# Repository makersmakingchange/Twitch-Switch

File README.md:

<!---  Open Source Assistive Technology: GitHub Readme Template Version 1.1 (2024-Mar-15)  --->

<!--- INSTRUCTIONS This is a markdown template for creating the README.md file in a GitHub repository. This file is rendered and displayed automatically when someone visits the repository.  --->  
 
 <!---  TITLE Should match the name of the GitHub repository. Choose something descriptive rather than whimsical.   --->
# Twitch Switch

<!---  SUMMARY A brief summary of the project. What it does, who it is for, how much it costs.  --->
The Twitch Switch is for users with limited movement capabilities. Up to three small wireless sensors can capture very small movements. The Twitch Switch can be used for activating up to three switch adapted devices or emulating a mouse or keyboard to operate a digital device such as a computer. 

The Twitch Switch works best for someone who is only able to perform small movements. There are three sensors that can be placed wherever the user has the most controlled, repeatable, intentional movement. Sensor placement can include on the user's finger, wrist, foot, or head. The sensors are powered by rechargeable batteries and connect wirelessly to a controller. The sensitivity of each sensor can be adjusted using knobs on the controller.

The first way to use the Twitch Switch allows the user to activate up to 3 switch adapted devices. Whenever the corresponding switch is moved (even slightly!), the switch adapted device will be activated. 
The second way to use the Twitch Switch is for controlling a digital device such as a computer, tablet, or smartphone. The Twitch Switch can connect via Bluetooth or USB, and has 3 modes: mouse mode, tablet mode, and keyboard mode (which is best for switch control).

The Twitch Switch is intended primarily for people who have some controlled, repeatable, intentional movement, but otherwise have limited mobility and/or dexterity. This device may be beneficial for users with cerebral palsy (CP), spinal cord injuries (SCI), amyotrophic lateral sclerosis (ALS), muscular dystrophy (MD), locked-in syndrome (LIS), traumatic brain injury (TBI), or other disabilities or conditions that significantly limit movement.

The total cost of materials to build this device is around \$360 (plus component shipping). The cost of materials per unit is around \$200 (plus component shipping) if you are able to build in bulk.

Note: for those located in Canada who are interested in this device, there are a limited number of Twitch Switches available free of cost. Please contact the Rehabilitation Engineering Department at the Stan Cassidy Centre for Rehabilitation at SCCRRehabEngineering@horizonnb.ca

## More info at
- [Makers Making Change Assistive Device Library Listing](https://www.makersmakingchange.com/s/product/twitch-switch/01tJR000003UiebYAC)

## How to Obtain the Device
### 1. Do-it-Yourself (DIY) or Do-it-Together (DIT)

This is an open-source assistive technology, so anyone is free to build it. All of the files and instructions required to build the device are contained within this repository. Refer to the Maker Guide below.

### 2. Request a build of this device

You may also submit a build request through the [Makers Making Change Assistive Device Listing](https://www.makersmakingchange.com/s/product/twitch-switch/01tJR000003UiebYAC) to have a volunteer maker build the device. As the requestor, you are responsible for reimbursing the maker for the cost of materials and any shipping.

### 3. Build this device for someone else

If you have the skills and equipment to build this device, and would like to donate your time to create the device for someone who needs it, visit the [MMC Maker Wanted](https://makersmakingchange.com/maker-wanted/) section.

## Build Instructions

### 1. Read through the Maker Guide

The [Maker Guide](/Documentation/Twitch_Switch_Maker_Guide.pdf) contains all the necessary information to build this device, including tool lists, assembly instructions, programming instructions and testing.

### 2. Order the Custom PCBs

This build requires two customs PCBS: one custom PCB for the controller and one custom PCB for each of the three sensors. The sensor PCB has a number of surface mount components and it is recommended to have the PCB fabricator assemble these components on the board.

### 3. Order the Off-The-Shelf Components

The [Bill of Materials](/Documentation/Twitch_Switch_BOM.csv) lists all of the parts and components required to build the device.

### 4. Print the 3D Printable components

All of the files and individual print files can be in the [/Build_Files/3D_Printing_Files](/Build_Files/3D_Printing_Files/) folder. Instructions and settings are provided in the 3D Printing Guide section of the [Maker Guide](/Documentation/Twitch_Switch_Maker_Guide.pdf).

### 5. Assemble the Twitch Switch

Reference the [Maker Guide](/Documentation/Twitch_Switch_Maker_Guide.pdf) for the tools and steps required to build each portion.

## How to improve this Device
As open source assistive technology, you are welcomed and encouraged to improve upon the design. 

## Files
### Documentation
| Document             | Version | Link |
|----------------------|---------|------|
| Maker Guide          | 1.0     | [Twitch Switch_Maker_Guide](/Documentation/Twitch_Switch_Maker_Guide.pdf)     |
| Bill of Materials    | 1.0     | [Twitch Switch_Bill_of_Materials](/Documentation/Twitch_Switch_BOM.csv)     |
| User Guide           | 1.0     | [Twitch Switch_User_Guide](/Documentation/Twitch_Switch_User_Guide.pdf)    |
| Changelog            | 1.0     | [Changelog](CHANGES.txt)     |

### Design Files
<!--- DESIGN FILES Include a copy of the original design files to facilitate easy editing and customization. Consider also including a generic format (e.g., STEP) --->
 - [CAD Files](/Design_Files/CAD_Design_Files)
 - [PCB Files](/Design_Files/PCB_Design_Files)

<!--- BUILD FILES Include a copy of the build files intended for manufacturing. This may include svg files for laser cutting, stl files for 3d printing, Gerber files for custom PCBs, and Arduino files for custom firmware --->
### Build Files
 - [3D Printing Files](/Build_Files/3D_Printing_Files)
 - [PCB Build Files](/Build_Files/PCB_Build_Files)
 - [Firmware Files](/Build_Files/Firmware_Files)

<!--- ATTRIBUTION Provide any necessary attribution for designs or components that are included in the device or as part of the project. --->
## Attribution

The Twitch Switch was designed by the Rehabilitation Engineering Department at Horizon Health's, Stan Cassidy Centre for Rehabilitation (SCCR).  Development was supported through the Government of Canada's Innovation Science and Economic Development [Accessible Technology Program](https://ised-isde.canada.ca/site/accessible-technology-program). The ATP program enabled SCCR to deploy numerous Twitch Switches to users at reduced cost.

The latest design (V3.0) incorporates feedback and suggestions from numerous users, clinicians, and volunteer makers.

The latest design incorporates several commercially available open source hardware components from [Adafruit](https://www.adafruit.com/). The Twitch Switch firmware utilizes the [Arduino](https://www.arduino.cc/) development platform, and a number of libraries developed and shared by the open source community.

<!---
This is the attribution for the template.
--->
The documentation template was created by Makers Making Change / Neil Squire Society and is used under a CC BY-SA 4.0 license. It is available at the following link: [https://github.com/makersmakingchange/OpenAT-Template](https://github.com/makersmakingchange/OpenAT-Template)

<!--- CONTRIBUTORS List the names of the people that contributed to the design. This could include the original source of the idea, designers, testers, documenters, etc. --->
### Contributors
- Rachelle Bernier, Horizon Health Network. 
- Marla Calder, Horizon Health Network 
- Natasha Hanson, Horizon Health Network 
- Dorian Hawkes, Horizon Health Network 
- Rick McCaskill, Horizon Health Network 
- Billie O'Connor, Horizon Health Network 
- Kristen Culberson, Horizon Health Network 
- Josie Versloot, Neil Squire Society / Makers Making Change
 
<!--- LICENSE Add the year(s) for the copyright and the Designer Name. You may use the standard set of open licenses or choose your own for the hardware, software, and accompanying materials. --->
## License
Copyright (c) 2020-2024 Stan Cassidy Center for Rehabilitation.

This repository describes Open Hardware:
 - Everything needed or used to design, make, test, or prepare the Twitch Switch is licensed under the [CERN 2.0 Weakly Reciprocal license (CERN-OHL-W v2) or later](https://cern.ch/cern-ohl ) .
 - All software is under the [GNU General Public License v3.0 (GPL-3.0)](https://www.gnu.org/licenses/gpl.html).
 - Accompanying material such as instruction manuals, videos, and other copyrightable works that are useful but not necessary to design, make, test, or prepare the Twitch Switch are published under a [Creative Commons Attribution-ShareAlike 4.0 license (CC BY-SA 4.0)](https://creativecommons.org/licenses/by-sa/4.0/) .

You may redistribute and modify this documentation and make products using it under the terms of the [CERN-OHL-W v2](https://cern.ch/cern-ohl).
This documentation is distributed WITHOUT ANY EXPRESS OR IMPLIED WARRANTY, INCLUDING OF MERCHANTABILITY, SATISFACTORY QUALITY AND FITNESS FOR A PARTICULAR PURPOSE.
Please see the CERN-OHL-W v2 for applicable conditions.

Source Location: https://github.com/makersmakingchange/Twitch-Switch

---

<!-- ABOUT MMC START -->
## About Makers Making Change

Makers Making Change is a program of [Neil Squire](https://www.neilsquire.ca/), a Canadian non-profit that uses technology, knowledge, and passion to empower people with disabilities.

Makers Making Change leverages the capacity of community based Makers, Disability Professionals and Volunteers to develop and deliver affordable Open Source Assistive Technologies.

 - Website: [www.MakersMakingChange.com](https://www.makersmakingchange.com/)
 - GitHub: [makersmakingchange](https://github.com/makersmakingchange)
 - Bluesky: [@makersmakingchange.bsky.social](https://bsky.app/profile/makersmakingchange.bsky.social)
 - Instagram: [@makersmakingchange](https://www.instagram.com/makersmakingchange)
 - Facebook: [makersmakechange](https://www.facebook.com/makersmakechange)
 - LinkedIn: [Neil Squire Society](https://www.linkedin.com/company/neil-squire-society/)
 - Thingiverse: [makersmakingchange](https://www.thingiverse.com/makersmakingchange/about)
 - Printables: [MakersMakingChange](https://www.printables.com/@MakersMakingChange)

### Contact Us
For technical questions, to get involved, or to share your experience we encourage you to [visit our website](https://www.makersmakingchange.com/) or [contact us](https://www.makersmakingchange.com/s/contact).
<!-- ABOUT MMC END -->

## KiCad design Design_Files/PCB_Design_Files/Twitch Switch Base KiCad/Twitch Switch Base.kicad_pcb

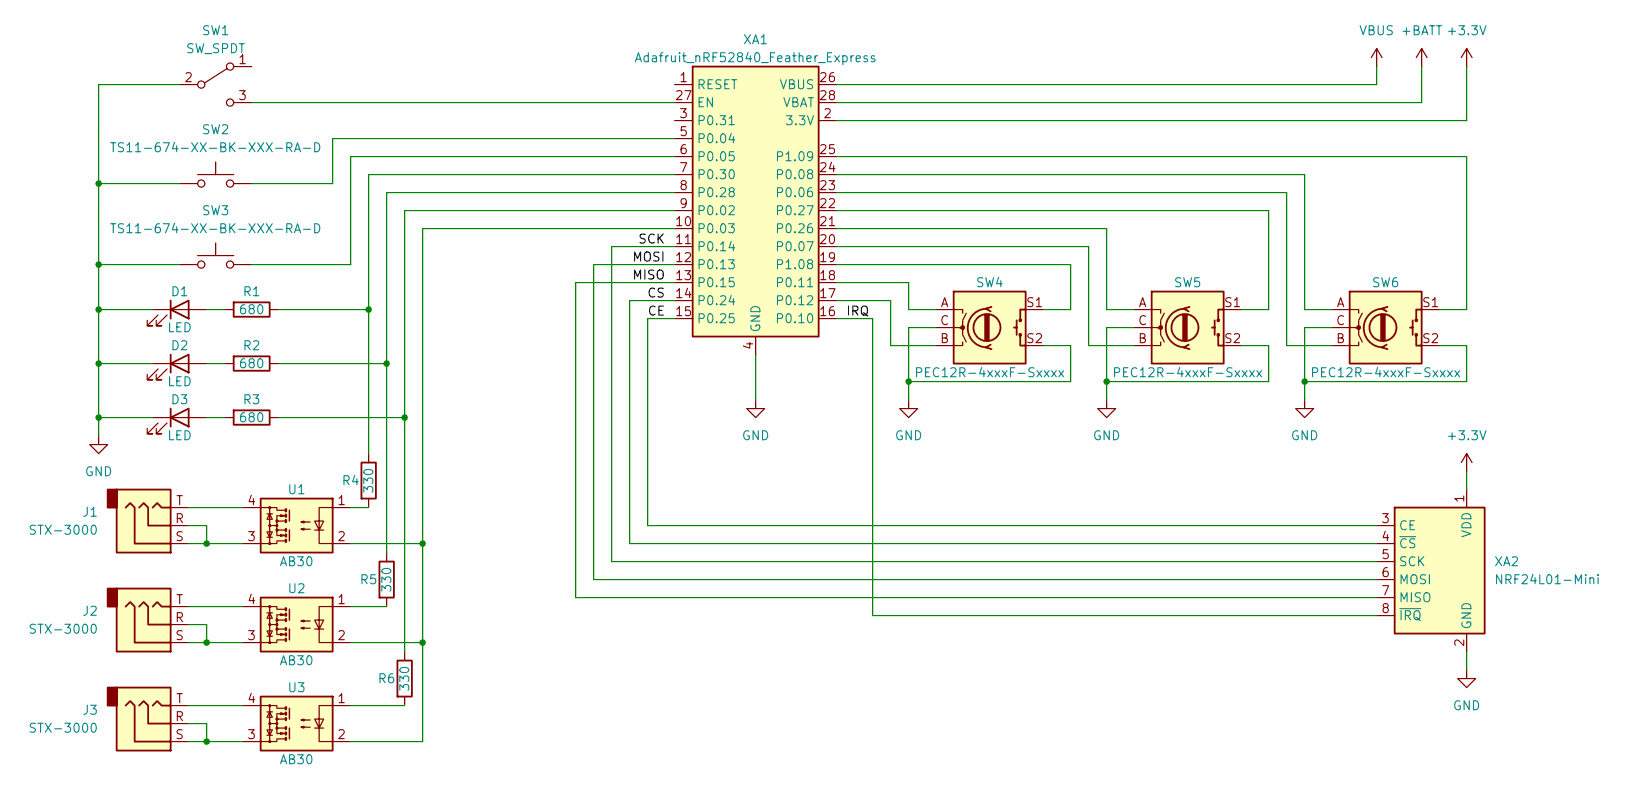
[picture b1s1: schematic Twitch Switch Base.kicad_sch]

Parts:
D1, D2, D3: LED; LED_D5.0mm
J1, J2, J3: STX-3000
R1, R2, R3: 680; R_Axial_DIN0207_L6.3mm_D2.5mm_P7.62mm_Horizontal
R4, R5, R6: 330; R_Axial_DIN0207_L6.3mm_D2.5mm_P7.62mm_Horizontal
SW1: SW_SPDT; CSS-1210TB
SW2, SW3: TS11-674-XX-BK-XXX-RA-D
SW4, SW5, SW6: PEC12R-4xxxF-Sxxxx
U1, U2, U3: AB30; DIP-4_W7.62mm
XA1: Adafruit_nRF52840_Feather_Express; Adafruit Feather nRF52840 Express
XA2: NRF24L01-Mini

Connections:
+3.3V: XA1.2 (3.3V), XA2.1 (VDD)
+BATT: XA1.28 (VBAT)
/CE: XA1.15 (P0.25), XA2.3 (CE)
/CS: XA1.14 (P0.24), XA2.4 (~CS)
/IRQ: XA1.16 (P0.10), XA2.8 (~IRQ)
/MISO: XA1.13 (P0.15), XA2.7 (MISO)
/MOSI: XA1.12 (P0.13), XA2.6 (MOSI)
/SCK: XA1.11 (P0.14), XA2.5 (SCK)
GND: D1.1 (K), D2.1 (K), D3.1 (K), SW1.2 (B), SW2.1, SW3.1, SW4.C, SW4.MP, SW4.S2, SW5.C, SW5.MP, SW5.S2, SW6.C, SW6.MP, SW6.S2, XA1.4 (GND), XA1.MNT1, XA1.MNT2, XA2.2 (GND), XA2.9 (GND)
unnamed: D1.2 (A), R1.2
unnamed: D2.2 (A), R2.2
unnamed: D3.2 (A), R3.2
unnamed: J1.R, J1.S, U1.3
unnamed: J1.T, U1.4
unnamed: J2.R, J2.S, U2.3
unnamed: J2.T, U2.4
unnamed: J3.R, J3.S, U3.3
unnamed: J3.T, U3.4
unnamed: R1.1, R4.1, XA1.7 (P0.30)
unnamed: R2.1, R5.1, XA1.8 (P0.28)
unnamed: R3.1, R6.1, XA1.9 (P0.02)
unnamed: R4.2, U1.1
unnamed: R5.2, U2.1
unnamed: R6.2, U3.1
unnamed: SW1.3 (C), XA1.27 (EN)
unnamed: SW2.2, XA1.5 (P0.04)
unnamed: SW3.2, XA1.6 (P0.05)
unnamed: SW4.A, XA1.18 (P0.11)
unnamed: SW4.B, XA1.17 (P0.12)
unnamed: SW4.S1, XA1.19 (P1.08)
unnamed: SW5.A, XA1.21 (P0.26)
unnamed: SW5.B, XA1.20 (P0.07)
unnamed: SW5.S1, XA1.22 (P0.27)
unnamed: SW6.A, XA1.24 (P0.08)
unnamed: SW6.B, XA1.23 (P0.06)
unnamed: SW6.S1, XA1.25 (P1.09)
unnamed: U1.2, U2.2, U3.2, XA1.10 (P0.03)
VBUS: XA1.26 (VBUS)

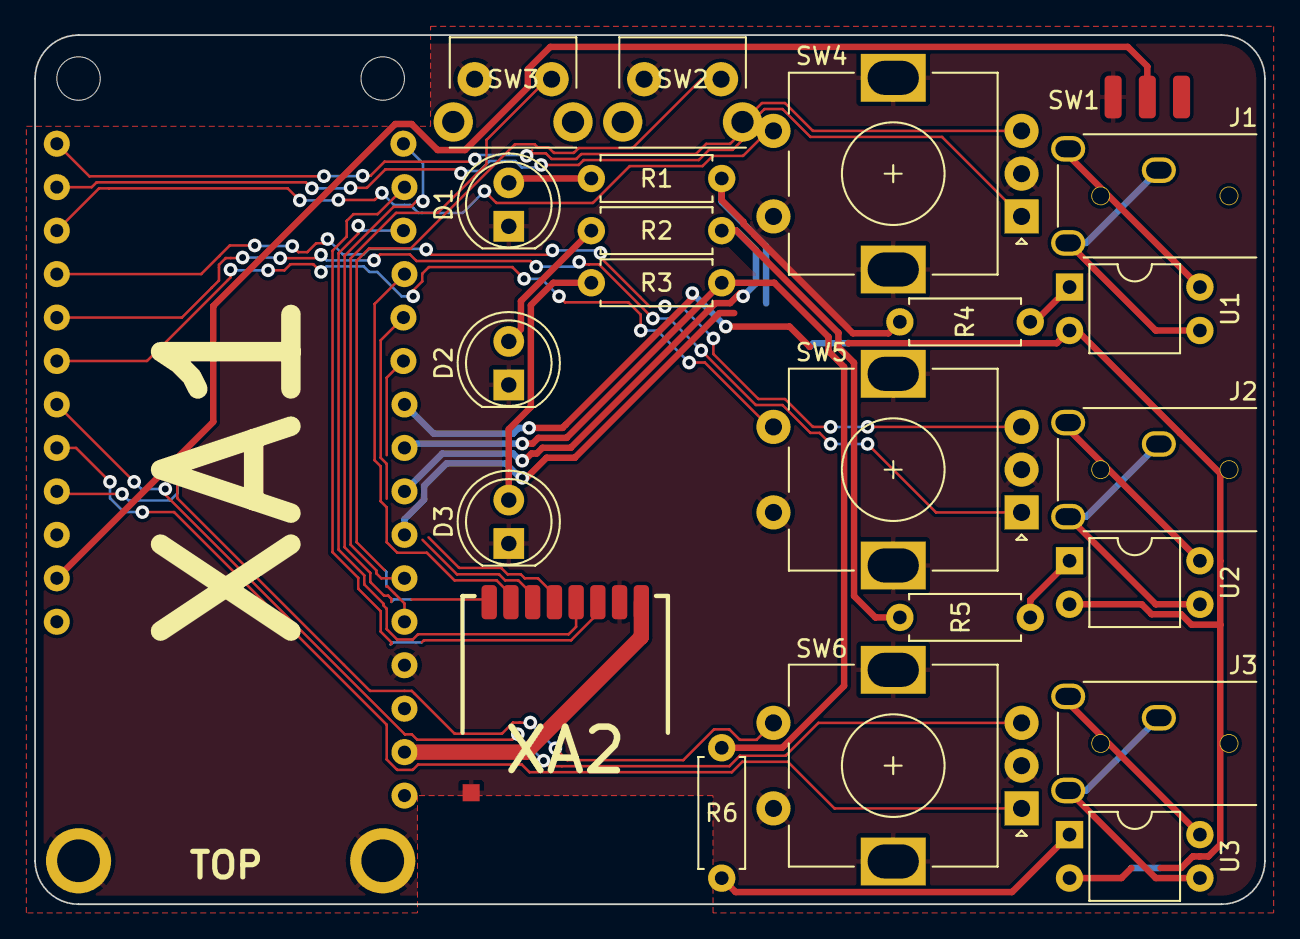
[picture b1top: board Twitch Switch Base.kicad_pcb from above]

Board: 2 copper layers, 71.9 x 50.8 mm, 23 parts (0 on the bottom side), 36 nets.

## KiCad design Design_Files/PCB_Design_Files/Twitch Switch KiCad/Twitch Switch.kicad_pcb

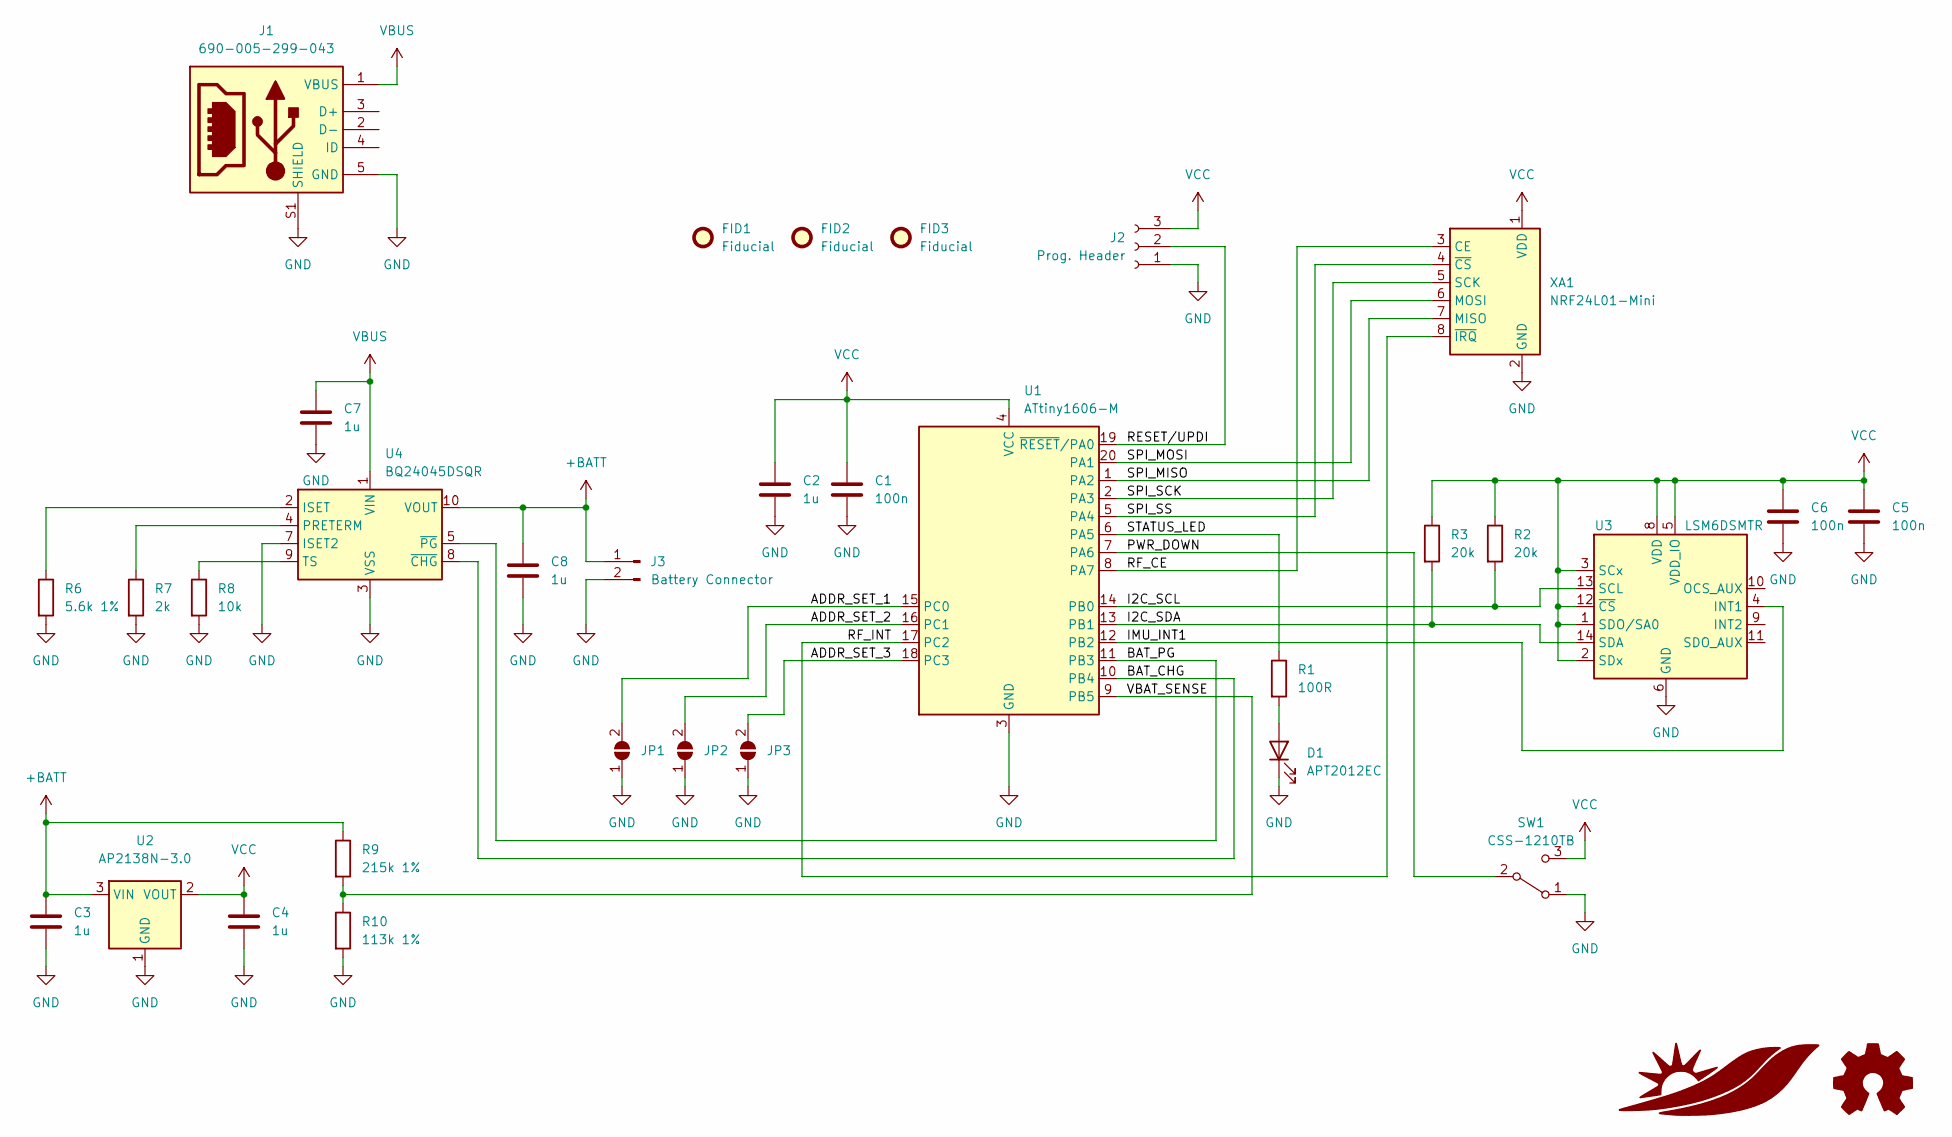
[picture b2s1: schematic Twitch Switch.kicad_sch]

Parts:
C1: 100n; C_0402_1005Metric; Part CL10B104KB8NNWC
C2, C3, C4, C7, C8: 1u; C_0402_1005Metric; Part CL10B105KP8NFNC
C5, C6: 100n; C_0402_1005Metric; Part CL10B105KP8NFNC
D1: APT2012EC; LED_0805_2012Metric; Part APT2012EC
FID1, FID2, FID3: Fiducial; Fiducial_0.5mm_Mask1mm
J1: 690-005-299-043
J2: Prog. Header; PinHeader_1x03_P2.54mm_Vertical
J3: Battery Connector; JST_PH_S2B-PH-K_1x02_P2.00mm_Horizontal; Part S2B-PH-K-S(LF)(SN)
JP1, JP2, JP3: SolderJumper_2_Open; SolderJumper-2_P1.3mm_Open_RoundedPad1.0x1.5mm
LOGO1: Logo_Open_Hardware_Small; OSHW-Logo_11.4x12mm_SilkScreen
LOGO2: Logo_Stan_Cassidy
R1: 100R; R_0402_1005Metric; Part RMCF0603JT100R
R2, R3: 20k; R_0402_1005Metric; Part RMCF0603JT20K0
R6: 5.6k 1%; R_0402_1005Metric; Part RMCF0603FT5K60
R7: 2k; R_0402_1005Metric; Part RMCF0603JT2K00
R8: 10k; R_0402_1005Metric; Part RMCF0603JT10K0
R9: 215k 1%; R_0402_1005Metric; Part RMCF0603FT215K
R10: 113k 1%; R_0402_1005Metric; Part RMCF0603FT113K
SW1: CSS-1210TB; Part CSS-1210TB
U1: ATtiny1606-M; VQFN-20-1EP_3x3mm_P0.4mm_EP1.7x1.7mm; Part ATtiny1606-MFR
U2: AP2138N-3.0; SOT-23; Part AP2138N-3.0TRG1
U3: LSM6DSMTR
U4: BQ24045DSQR; Part BQ24045DSQR
XA1: NRF24L01-Mini; Part NRF24L01-Mini

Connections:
+BATT: C3.2, C8.2, J3.1, R9.1, U2.3 (VIN), U4.10 (VOUT)
/ADDR_SET_1: JP1.2 (B), U1.15 (PC0)
/ADDR_SET_2: JP2.2 (B), U1.16 (PC1)
/ADDR_SET_3: JP3.2 (B), U1.18 (PC3)
/BAT_CHG: U1.10 (PB4), U4.8 (~CHG)
/BAT_PG: U1.11 (PB3), U4.5 (~PG)
/I2C_SCL: R2.2, U1.14 (PB0), U3.13 (SCL)
/I2C_SDA: R3.2, U1.13 (PB1), U3.14 (SDA)
/IMU_INT1: U1.12 (PB2), U3.4 (INT1)
/PWR_DOWN: SW1.2 (B), U1.7 (PA6)
/RESET/UPDI: J2.2, U1.19 (~RESET/PA0)
/RF_CE: U1.8 (PA7), XA1.3 (CE)
/RF_INT: U1.17 (PC2), XA1.8 (~IRQ)
/SPI_MISO: U1.1 (PA2), XA1.7 (MISO)
/SPI_MOSI: U1.20 (PA1), XA1.6 (MOSI)
/SPI_SCK: U1.2 (PA3), XA1.5 (SCK)
/SPI_SS: U1.5 (PA4), XA1.4 (~CS)
/STATUS_LED: R1.1, U1.6 (PA5)
/VBAT_SENSE: R9.2, R10.1, U1.9 (PB5)
GND: C1.1, C2.1, C3.1, C4.1, C5.1, C6.1, C7.1, C8.1, D1.1 (K), J1.5 (GND), J1.S1 (SHIELD), J1.S2 (SHIELD), J1.S3 (SHIELD), J1.S4 (SHIELD), J2.1, J3.2, JP1.1 (A), JP2.1 (A), JP3.1 (A), R6.2, R7.2, R8.2, R10.2, SW1.1 (A), U1.3 (GND), U1.21 (GND), U2.1 (GND), U3.6 (GND), U3.7 (GND), U4.3 (VSS), U4.7 (ISET2), U4.11 (VSS), XA1.2 (GND), XA1.9 (GND)
unnamed: D1.2 (A), R1.2
unnamed: R6.1, U4.2 (ISET)
unnamed: R7.1, U4.4 (PRETERM)
unnamed: R8.1, U4.9 (TS)
VBUS: C7.2, J1.1 (VBUS), U4.1 (VIN)
VCC: C1.2, C2.2, C4.2, C5.2, C6.2, J2.3, R2.1, R3.1, SW1.3 (C), U1.4 (VCC), U2.2 (VOUT), U3.1 (SDO/SA0), U3.2 (SDx), U3.3 (SCx), U3.5 (VDD_IO), U3.8 (VDD), U3.12 (~CS), XA1.1 (VDD)

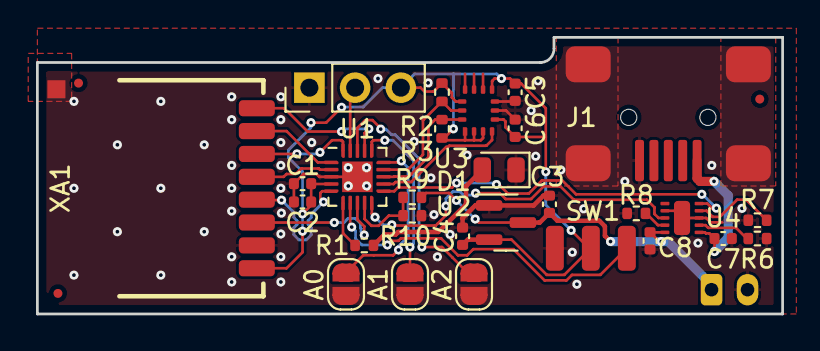
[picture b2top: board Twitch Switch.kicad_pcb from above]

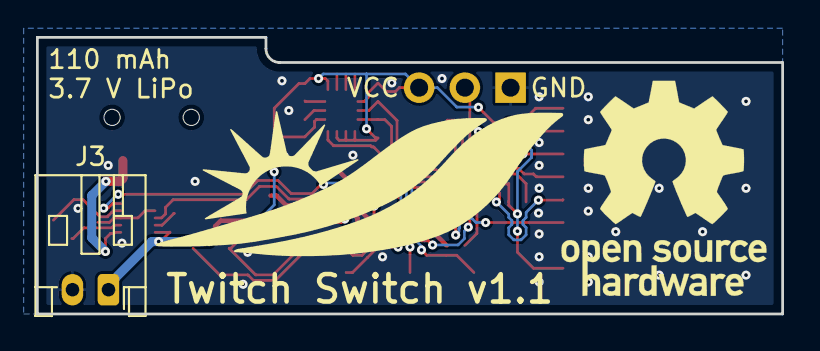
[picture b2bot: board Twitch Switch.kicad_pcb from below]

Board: 2 copper layers, 41.4 x 15.4 mm, 34 parts (3 on the bottom side), 26 nets.

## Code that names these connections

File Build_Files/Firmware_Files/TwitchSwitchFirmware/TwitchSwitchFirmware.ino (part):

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#define WM_LEVEL 192
#define WU_THRESHOLD 2

RF24 radio(PIN_RF_CE, PIN_SPI_SS);
lsm6dsm imu;

uint8_t readbuf[32];
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  byte flags_c = VPORTC.INTFLAGS;

  // 1st - check if it was the power switch
  // Power is on PORTA PA6, so check there
  if (flags_a & (1 << 6)) {
    handlePowerSwitch = 1;
    VPORTA.INTFLAGS |= (1 << 6);
  }

  // 1st - check if it was the IMU that interrupted
  // IMU_INT1 is on PB2, so check there
  if (flags_b & (1 << 2)) {
    handleIMUInterrupt = 1;
    VPORTB.INTFLAGS |= (1 << 2);
  }

  // BAT_PG is on PB3
  if (flags_b & (1 << 3)) {
    handleBatPG = 1;
    VPORTB.INTFLAGS |= (1 << 3);
  }

  // BAT_CHG is on PB4
  if (flags_b & (1 << 4)) {
    handleBatCharge = 1;
    VPORTB.INTFLAGS |= (1 << 4);
  }

  // PIN_VBAT_SENSE is on PB5
  if (flags_b & (1 << 5)) {
    handleBatSense = 1;
    VPORTB.INTFLAGS |= (1 << 5);
  }
  

  // RADIO_INT is on PC2
  if (flags_c & (1 << 2)) {
    handleRadioInterrupt = 1;
    VPORTC.INTFLAGS |= (1 << 2);
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  // Take remainder of previous division and multiply by 2^16 for the alarm compare: 0.86645508*2^16 = 56784

  TCA0.SINGLE.CMP0 = TCA0.SINGLE.CNT + 39062;
  digitalWriteFast(PIN_STATUS_LED, !digitalReadFast(PIN_STATUS_LED));
}
*/

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  set_sleep_mode(SLEEP_MODE_IDLE); // Use standby for 100x less power, but only if you don't need TCA0
  sleep_enable();

  pinConfigure(PIN_STATUS_LED, OUTPUT);
  //For more details about configuring pins on the ATtiny - sell https://github.com/SpenceKonde/megaTinyCore/blob/master/megaavr/extras/Ref_Digital.md

  //Configure the pins so that we can read which switch this is (1,2,3)
  pinConfigure(PIN_PC0, PIN_PULLUP | PIN_DIR_INPUT);
  pinConfigure(PIN_PC1, PIN_PULLUP | PIN_DIR_INPUT);
  pinConfigure(PIN_PC3, PIN_PULLUP | PIN_DIR_INPUT);

  pinConfigure(PIN_IMU_INT1, PIN_DIR_INPUT | PIN_ISC_RISE);
  pinConfigure(PIN_PWR_DOWN, PIN_DIR_INPUT | PIN_ISC_CHANGE);


  pinConfigure(PIN_BAT_PG, PIN_DIR_INPUT | PIN_ISC_CHANGE);
  pinConfigure(PIN_BAT_CHG, PIN_DIR_INPUT | PIN_ISC_CHANGE);
  pinConfigure(PIN_VBAT_SENSE, PIN_DIR_INPUT | PIN_ISC_CHANGE);

  delay(15);

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
  // We can save some power by turning off the pads we read as grounded (soldered)
  if (!(configPins & (1 << 3))) {
    // PC3 IS soldered
    pinConfigure(PIN_PC3, PIN_DIR_INPUT);
  }
  if (!(configPins & (1 << 1))) {
    // PC1 IS soldered
    pinConfigure(PIN_PC1, PIN_DIR_INPUT);
  }
  if (!(configPins & (1 << 0))) {
    // PC0 IS soldered
    pinConfigure(PIN_PC0, PIN_DIR_INPUT);
  }
  //1010, 1001, 0011

  //Initial mode (on / off) based on the power switch
  if (digitalReadFast(PIN_PWR_DOWN) == 1) {
    //ON
    mode = MODE_WAITING; 
  }
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  radio.stopListening();
}

bool isCharging = false; //digitalReadFast(PIN_BAT_CHG);

void startCharging()
{
  digitalWriteFast(PIN_STATUS_LED, HIGH);
  isCharging = true;
}

void stopCharging()
{
  digitalWriteFast(PIN_STATUS_LED, LOW);
  isCharging = false;
}

void blinkLED(long msDelay)
{
  for (uint8_t i = 0; i < 10; i++) {
    digitalWriteFast(PIN_STATUS_LED, !digitalReadFast(PIN_STATUS_LED));
    delay(msDelay);
  }
  digitalWriteFast(PIN_STATUS_LED, LOW);
}

// Note - this is blocking. Don't use in production. Debugging only.
void breathLED()
{
  for (uint8_t i = 0; i < 255; i++) {
    analogWrite(PIN_STATUS_LED, i);
    delay(5);
  }

  for (uint8_t i = 255; i > 0; i--) {
    analogWrite(PIN_STATUS_LED, i);
    delay(5);
  }
  digitalWriteFast(PIN_STATUS_LED, LOW);

}

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{

/*
  // Note Feb 2, 2024.PIN_BAT_CHG NOT high when charging. PIN_BAT_CHG is seemingly NEVER high...
  // From DOCS: CHG 8 8 O Low (FET on) indicates charging and Open Drain (FET off) indicates no Charging or Charge complete
  if (digitalReadFast(PIN_BAT_PG) == LOW)
  {
    digitalWriteFast(PIN_STATUS_LED, HIGH);
    //startCharging();
  }
  else
  {
    digitalWriteFast(PIN_STATUS_LED, LOW);
    //stopCharging();

  }
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  //const float R9 = 215000.0; // Put exact value here
  //const float R10 = 113000.0; // Put exact value here
  //const float Vref = 3.7;   // Put exact value here
  //int adcReading = analogRead(PIN_VBAT_SENSE);
  //float voltage = (R9+R10)/R9 * adcReading * Vref / 1024.0;

/*
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    handleBatCharge = 0;
    sei();  // Enable interrupts

    if (digitalReadFast(PIN_BAT_CHG))
      startCharging();
    else
      stopCharging();
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    handlePowerSwitch = 0;
    sei();  // Enable interrupts

    if (digitalReadFast(PIN_PWR_DOWN) == 1)
    {
      //Power is now ON, blink 5 times to indicate 'power on' change)
      blinkLED(100);
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        //We're OFF

        //The power switch was turned on
        if (digitalReadFast(PIN_PWR_DOWN) == 1) {
          transitionToWaiting();
        } 
        else
        {
          //Turn off LED UNLESS we're charging...
          if (!isCharging)
            digitalWriteFast(PIN_STATUS_LED, LOW);

          sleep_cpu();
        }
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    case MODE_WAITING:
      {
        //The power switch was turned off
        if (digitalReadFast(PIN_PWR_DOWN) == 0) {
          transitionToOff();
          break;
        }
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    case MODE_SENDING:
      {
        //The power switch was turned off
        if (digitalReadFast(PIN_PWR_DOWN) == 0) {
          transitionToOff();
          break;
        }
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        uint16_t fifo_level;  //this is in WORDS
        uint8_t wm_flag;      //watermark full?

        uint16_t vbatReading = analogRead(PIN_VBAT_SENSE); //Needs two bytes to send this over the radio since our array is (uint8)
        uint8_t imu_data[29]; //Grew from 27 so that we can send battery info over as well

        if (imu.available(&fifo_level, &wm_flag)) {
          //Something went wrong
          for (uint8_t i = 0; i < 10; i++) {
            digitalWriteFast(PIN_STATUS_LED, !digitalReadFast(PIN_STATUS_LED));
            delay(2000);
          }
        } 
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          uint8_t _failCounter = 0;
          while (fifo_level >= 12)
          {
digitalWriteFast(PIN_STATUS_LED, HIGH);

            //we have 24 bytes
            //move the bytes from the fifo to a buffer then to the radio
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
              //Fast blink LED so that we can 'see' the error
              for (uint8_t i = 0; i < 6; i++) {
                digitalWriteFast(PIN_STATUS_LED, !digitalReadFast(PIN_STATUS_LED));
                delay(100);
              }
              //Make sure we leave the LED on
              digitalWriteFast(PIN_STATUS_LED, HIGH);

              transitionToWaiting();
              packetnum = 0;
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            }
          }

 digitalWriteFast(PIN_STATUS_LED, LOW);
        }
        
        //If we're sending and PIN_IMU_INT1 PIN_PB2 is LOW, go to sleep?
        if (mode == MODE_SENDING && digitalReadFast(PIN_IMU_INT1) != 1) sleep_cpu();
      }
      break;
    
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  while (imu.begin())
    ;

  digitalWriteFast(PIN_STATUS_LED, LOW);

  imu.setWUDuration(2); //2 what?
  imu.setWUThreshold(WU_THRESHOLD);
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  imu.enableWMInterrupt();
  // Everything is already on, swap WU for WM interrupt
  
  //digitalWriteFast(PIN_STATUS_LED, HIGH);
}

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
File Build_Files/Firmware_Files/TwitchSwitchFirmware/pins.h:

#ifndef __PINS_H__
#define __PINS_H__

// All pins not explicitly defined here are
// taken care of already. This includes I2C and SPI,
// including chip-select.

// Output
#define PIN_STATUS_LED PIN_PA5
#define PIN_RF_CE PIN_PA7

// Input with interrupt on change
#define PIN_PWR_DOWN PIN_PA6

// Input with interrupt on change
#define PIN_IMU_INT1 PIN_PB2
#define PIN_BAT_PG PIN_PB3
#define PIN_BAT_CHG PIN_PB4

// Analog input
#define PIN_VBAT_SENSE PIN_PB5

// Input with interrupt on change
#define PIN_RF_INT PIN_PC2

#endif  /*PINS_H*/

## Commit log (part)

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2024-03-28 Added firmware zip files
2024-11-06 Version 3.1 - Updated Sensor Programmer
    Sensor programmer - wiring has been updated, resistor removed, and changed the diode. Maker Guide and BOM have been updated to reflect these changes. Typo in Maker Guide fixed.
2025-04-10 Add Update About MMC GitHub Action
2025-04-12 Update About MMC Section
2026-02-10 Update TS_Controller_Fabrication.zip
    Fixed tactile switch hole location

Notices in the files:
Build_Files/Firmware_Files/TwitchSwitchFirmware/TwitchSwitchFirmware.ino:
(C)2023 STAN CASSIDY CENTER FOR REHABILITATION (SCCR)
README.md:
List of open source licenses. Hardware: CERN-OHL-W-2.0, Software: GPL-3.0-or-later, Documentation: CC-BY-SA-4.0.
